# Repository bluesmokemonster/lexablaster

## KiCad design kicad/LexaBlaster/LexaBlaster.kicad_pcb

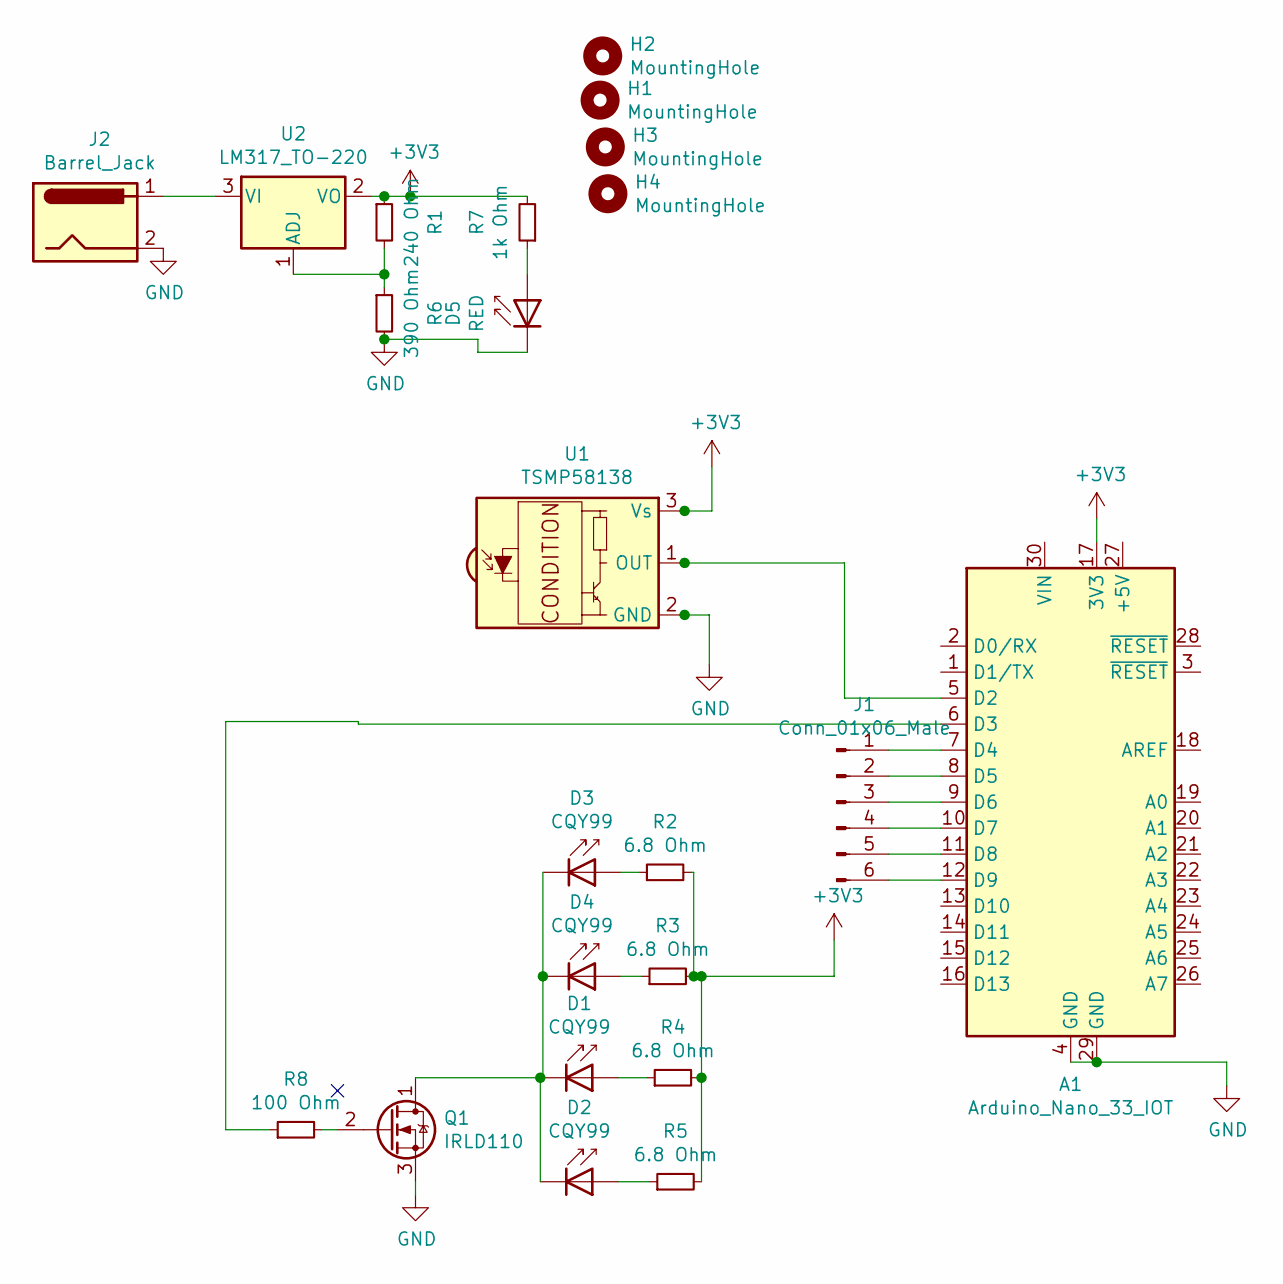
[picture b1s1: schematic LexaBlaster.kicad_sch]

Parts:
A1: Arduino_Nano_33_IOT; Arduino_Nano
D1, D2, D3, D4: CQY99; LED_D5.0mm_IRGrey
D5: RED; LED_D5.0mm_IRGrey
H1, H2, H3, H4: MountingHole; MountingHole_3.2mm_M3
J1: Conn_01x06_Male; PhoenixContact_MSTBA_2,5_6-G-5,08_1x06_P5.08mm_Horizontal
J2: Barrel_Jack; BarrelJack_Horizontal
Q1: IRLD110
R1: 240 Ohm; R_Axial_DIN0411_L9.9mm_D3.6mm_P15.24mm_Horizontal
R2, R3, R4, R5: 6.8 Ohm; R_Axial_DIN0411_L9.9mm_D3.6mm_P15.24mm_Horizontal
R6: 390 Ohm; R_Axial_DIN0411_L9.9mm_D3.6mm_P15.24mm_Horizontal
R7: 1k Ohm; R_Axial_DIN0411_L9.9mm_D3.6mm_P15.24mm_Horizontal
R8: 100 Ohm; R_Axial_DIN0207_L6.3mm_D2.5mm_P10.16mm_Horizontal
U1: TSMP58138; Vishay_MINICAST-3Pin
U2: LM317_TO-220; TO-220-3_Vertical

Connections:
+3V3: A1.17 (3V3), R1.1, R2.2, R3.2, R4.2, R5.2, R7.2, U1.3 (Vs), U2.2 (VO)
GND: A1.4 (GND), A1.29 (GND), D5.1 (K), J2.2, Q1.3 (S), R6.2, U1.2 (GND)
unnamed: A1.5 (D2), U1.1 (OUT)
unnamed: A1.6 (D3), R8.1
unnamed: A1.7 (D4), J1.1
unnamed: A1.8 (D5), J1.2
unnamed: A1.9 (D6), J1.3
unnamed: A1.10 (D7), J1.4
unnamed: A1.11 (D8), J1.5
unnamed: A1.12 (D9), J1.6
unnamed: D1.1 (K), D2.1 (K), D3.1 (K), D4.1 (K), Q1.1 (D)
unnamed: D1.2 (A), R4.1
unnamed: D2.2 (A), R5.1
unnamed: D3.2 (A), R2.1
unnamed: D4.2 (A), R3.1
unnamed: D5.2 (A), R7.1
unnamed: J2.1, U2.3 (VI)
unnamed: Q1.2 (G), R8.2
unnamed: R1.2, R6.1, U2.1 (ADJ)

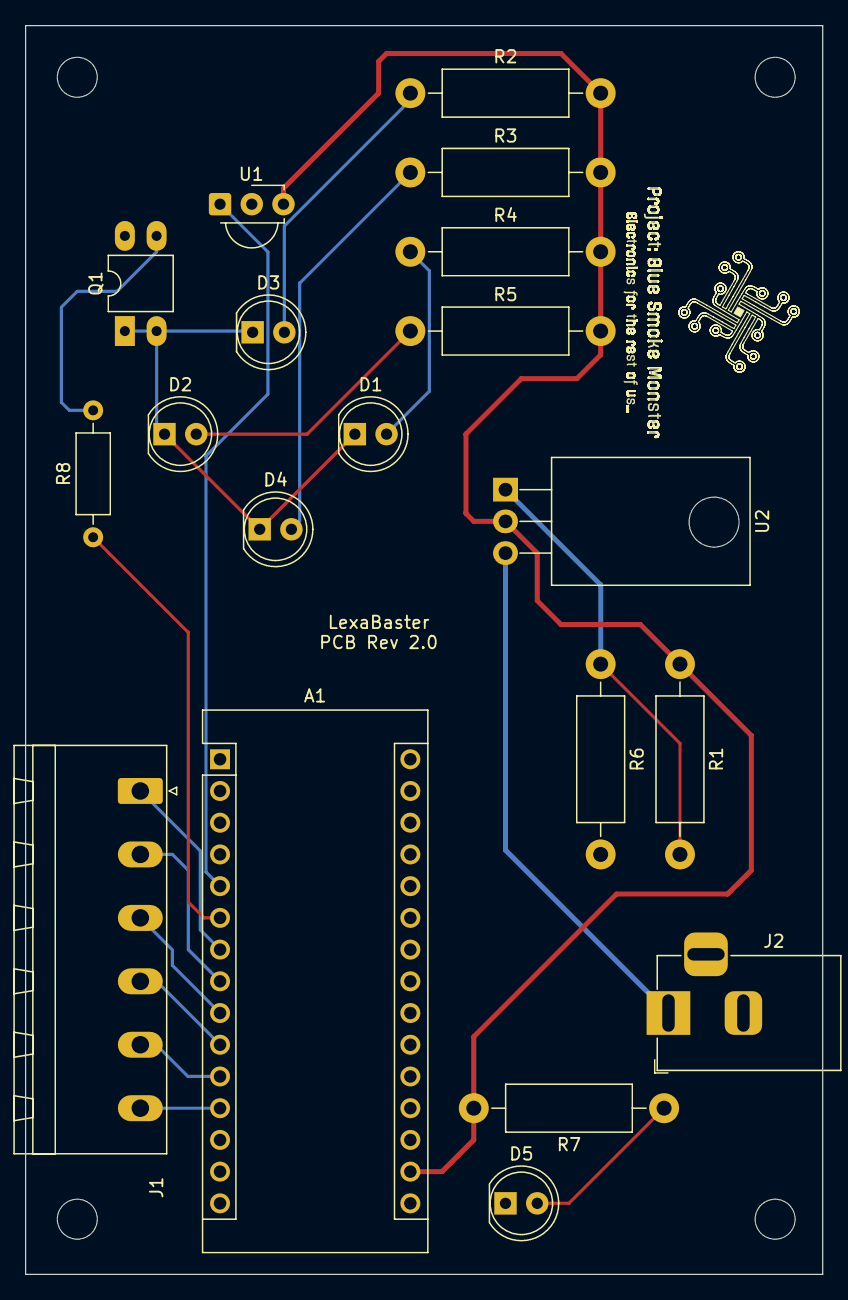
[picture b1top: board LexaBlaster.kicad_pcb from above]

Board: 2 copper layers, 63.8 x 100.0 mm, 23 parts (0 on the bottom side), 19 nets.

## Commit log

2021-07-17 Initial Commit
    Initial Commit
